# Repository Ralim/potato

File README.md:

# Potato

OpenSource inline USB-PD Power meter.

...WIP...

## Desired features

- Easy to assemble (No QFN)
- Read device PD capabilities
- Capture USB-PD messages
- Read USB D- / D+ voltages for QC
- Pull resistors for QC control
- UART or USB for datalogging
- Either buttons or encoder for input
- Small LCD display
- DC In/Out port

- Accelerometer or tilt switch for rotation?

## Ideas to explore

- As LVGL is a goal for the UI, consider [prototyping](https://docs.lvgl.io/latest/en/html/get-started/pc-simulator.html) on "real" computer or talking to the PineTime team about their experience about developing [UI in NaCL](https://github.com/AppKaki/lvgl-wasm), allowing feedback from web users. If realized, this may allow more explorative development in a less painful environment as you can skip the slow upload/reboot cycle.

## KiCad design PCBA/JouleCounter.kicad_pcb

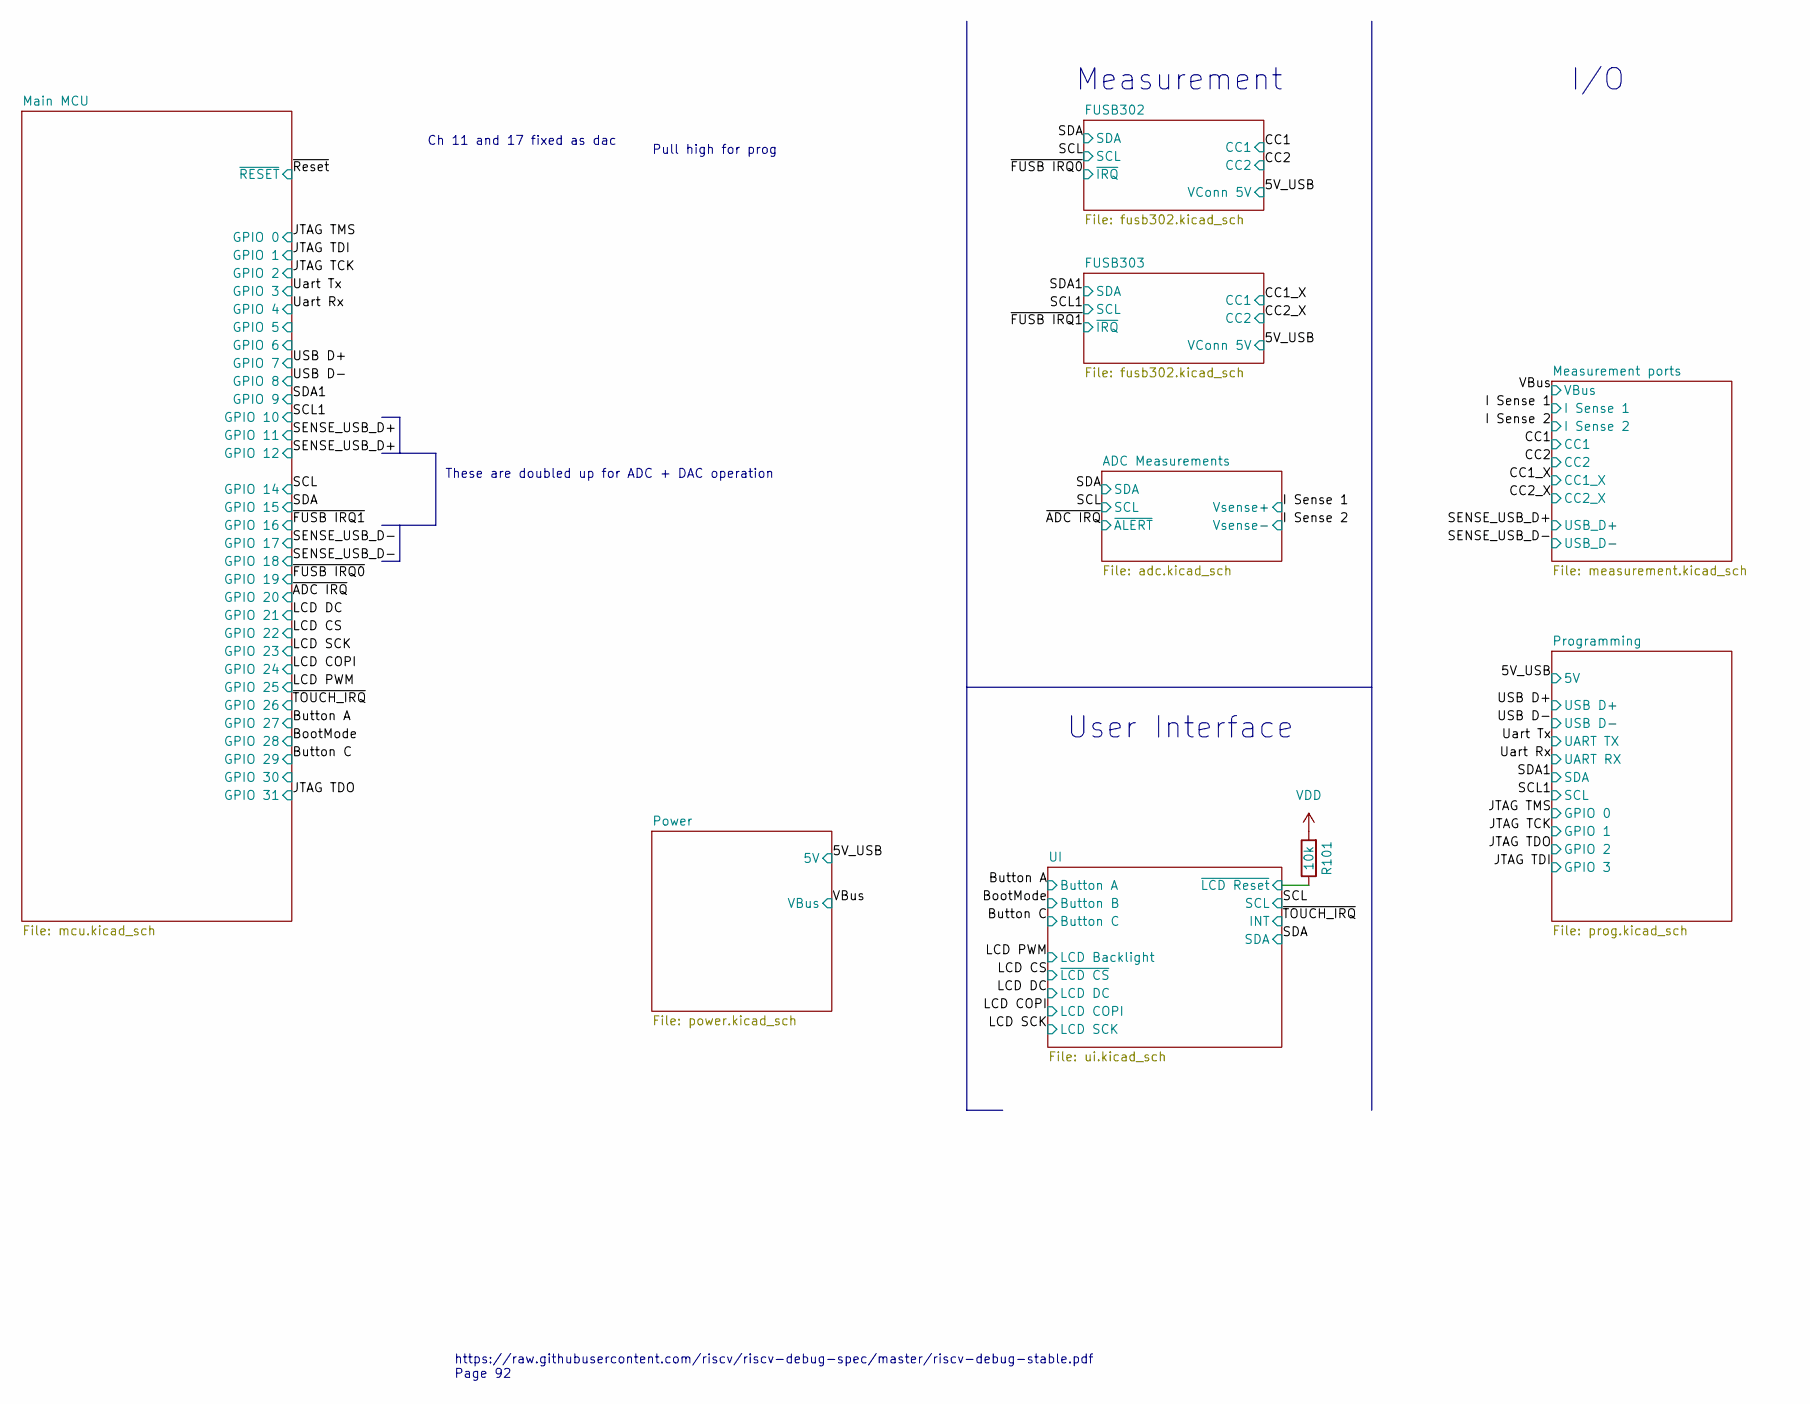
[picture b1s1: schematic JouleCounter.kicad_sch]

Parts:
R101: 10k; R_0603_1608Metric

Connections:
/UI/~LCD Reset: R101.1; also elsewhere on the board
VDD: R101.2; also elsewhere on the board

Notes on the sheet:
Measurement
Pull high for prog
I/O
Ch 11 and 17 fixed as dac
https://raw.githubusercontent.com/riscv/riscv-debug-spec/master/riscv-debug-stable.pdf Page 92
These are doubled up for ADC + DAC operation
User Interface

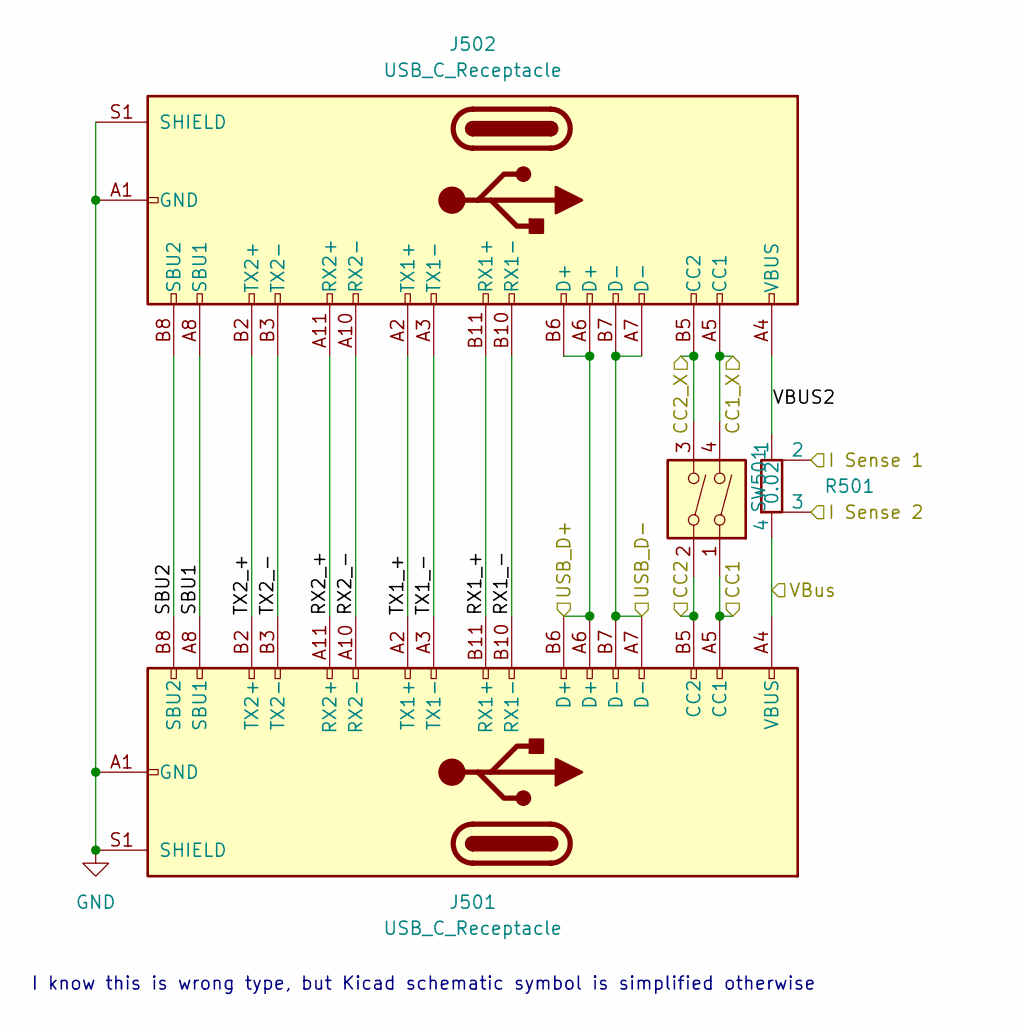
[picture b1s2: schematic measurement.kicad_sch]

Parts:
J501: USB_C_Receptacle; USB_C_Plug_JAE_DX07P024AJ1
J502: USB_C_Receptacle; USB_C_Receptacle_Amphenol_12401610E4-2A
R501: 0.02; R_Shunt_Vishay_WSK2512_6332Metric_T1.19mm
SW501: SW_DIP_x02; SW_DIP_SPSTx02_Slide_Copal_CHS-02A_W5.08mm_P1.27mm_JPin

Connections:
/CC1: J501.A5 (CC1), SW501.1; also elsewhere on the board
/CC1_X: J502.A5 (CC1), SW501.4; also elsewhere on the board
/CC2: J501.B5 (CC2), SW501.2; also elsewhere on the board
/CC2_X: J502.B5 (CC2), SW501.3; also elsewhere on the board
/I Sense 1: R501.2; also elsewhere on the board
/I Sense 2: R501.3; also elsewhere on the board
/Measurement ports/RX1_+: J501.B11 (RX1+), J502.B11 (RX1+)
/Measurement ports/RX1_-: J501.B10 (RX1-), J502.B10 (RX1-)
/Measurement ports/RX2_+: J501.A11 (RX2+), J502.A11 (RX2+)
/Measurement ports/RX2_-: J501.A10 (RX2-), J502.A10 (RX2-)
/Measurement ports/SBU1: J501.A8 (SBU1), J502.A8 (SBU1)
/Measurement ports/SBU2: J501.B8 (SBU2), J502.B8 (SBU2)
/Measurement ports/TX1_+: J501.A2 (TX1+), J502.A2 (TX1+)
/Measurement ports/TX1_-: J501.A3 (TX1-), J502.A3 (TX1-)
/Measurement ports/TX2_+: J501.B2 (TX2+), J502.B2 (TX2+)
/Measurement ports/TX2_-: J501.B3 (TX2-), J502.B3 (TX2-)
/Measurement ports/VBUS2: J502.A4 (VBUS), J502.A9 (VBUS), J502.B4 (VBUS), J502.B9 (VBUS), R501.1
/SENSE_USB_D+: J501.A6 (D+), J501.B6 (D+), J502.A6 (D+), J502.B6 (D+); also elsewhere on the board
/SENSE_USB_D-: J501.A7 (D-), J501.B7 (D-), J502.A7 (D-), J502.B7 (D-); also elsewhere on the board
/VBus: J501.A4 (VBUS), J501.A9 (VBUS), J501.B4 (VBUS), J501.B9 (VBUS), R501.4; also elsewhere on the board
GND: J501.A1 (GND), J501.A12 (GND), J501.B1 (GND), J501.B12 (GND), J501.S1 (SHIELD), J502.A1 (GND), J502.A12 (GND), J502.B1 (GND), J502.B12 (GND), J502.S1 (SHIELD); also elsewhere on the board

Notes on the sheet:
I know this is wrong type, but Kicad schematic symbol is simplified otherwise

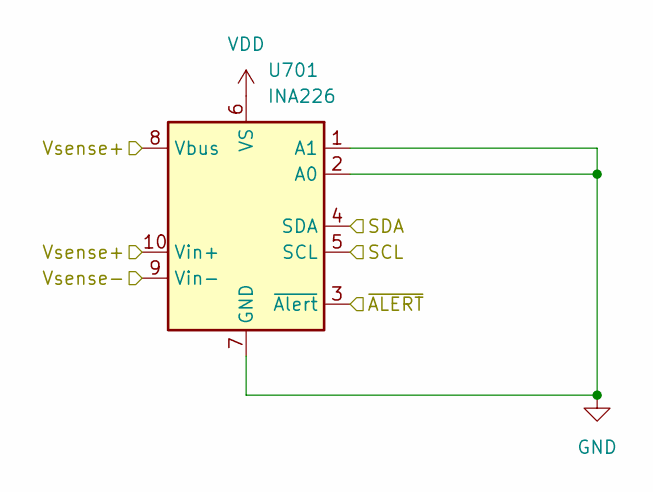
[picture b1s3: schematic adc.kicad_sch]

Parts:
U701: INA226; VSSOP-10_3x3mm_P0.5mm

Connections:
/I Sense 1: U701.8 (Vbus), U701.10 (Vin+); also elsewhere on the board
/I Sense 2: U701.9 (Vin-); also elsewhere on the board
/SCL: U701.5 (SCL); also elsewhere on the board
/SDA: U701.4 (SDA); also elsewhere on the board
/~ADC IRQ: U701.3 (~Alert); also elsewhere on the board
GND: U701.1 (A1), U701.2 (A0), U701.7 (GND); also elsewhere on the board
VDD: U701.6 (VS); also elsewhere on the board

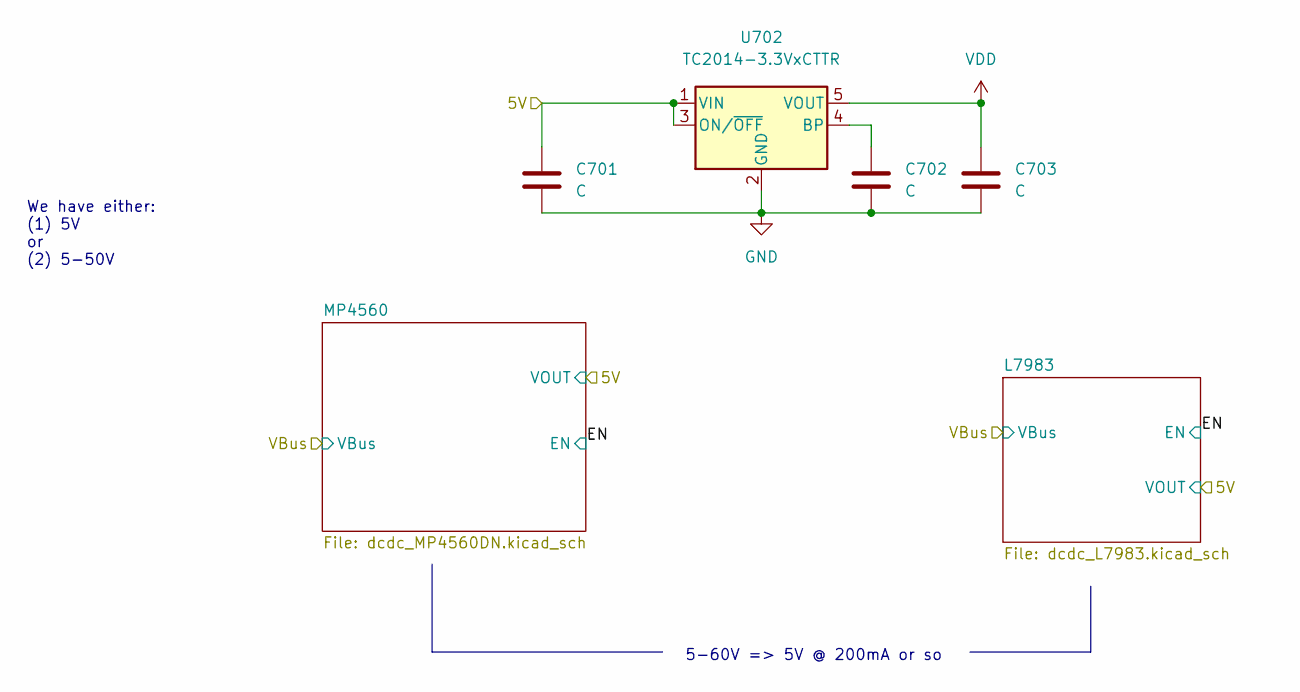
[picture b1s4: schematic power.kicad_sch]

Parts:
C701, C702, C703: C; C_0603_1608Metric
U702: TC2014-3.3VxCTTR; SOT-23-5

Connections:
/5V_USB: C701.1, U702.1 (VIN), U702.3 (ON/~OFF); also elsewhere on the board
GND: C701.2, C702.2, C703.2, U702.2 (GND); also elsewhere on the board
unnamed: C702.1, U702.4 (BP)
VDD: C703.1, U702.5 (VOUT); also elsewhere on the board

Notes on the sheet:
We have either: (1) 5V or (2) 5-50V
5-60V => 5V @ 200mA or so

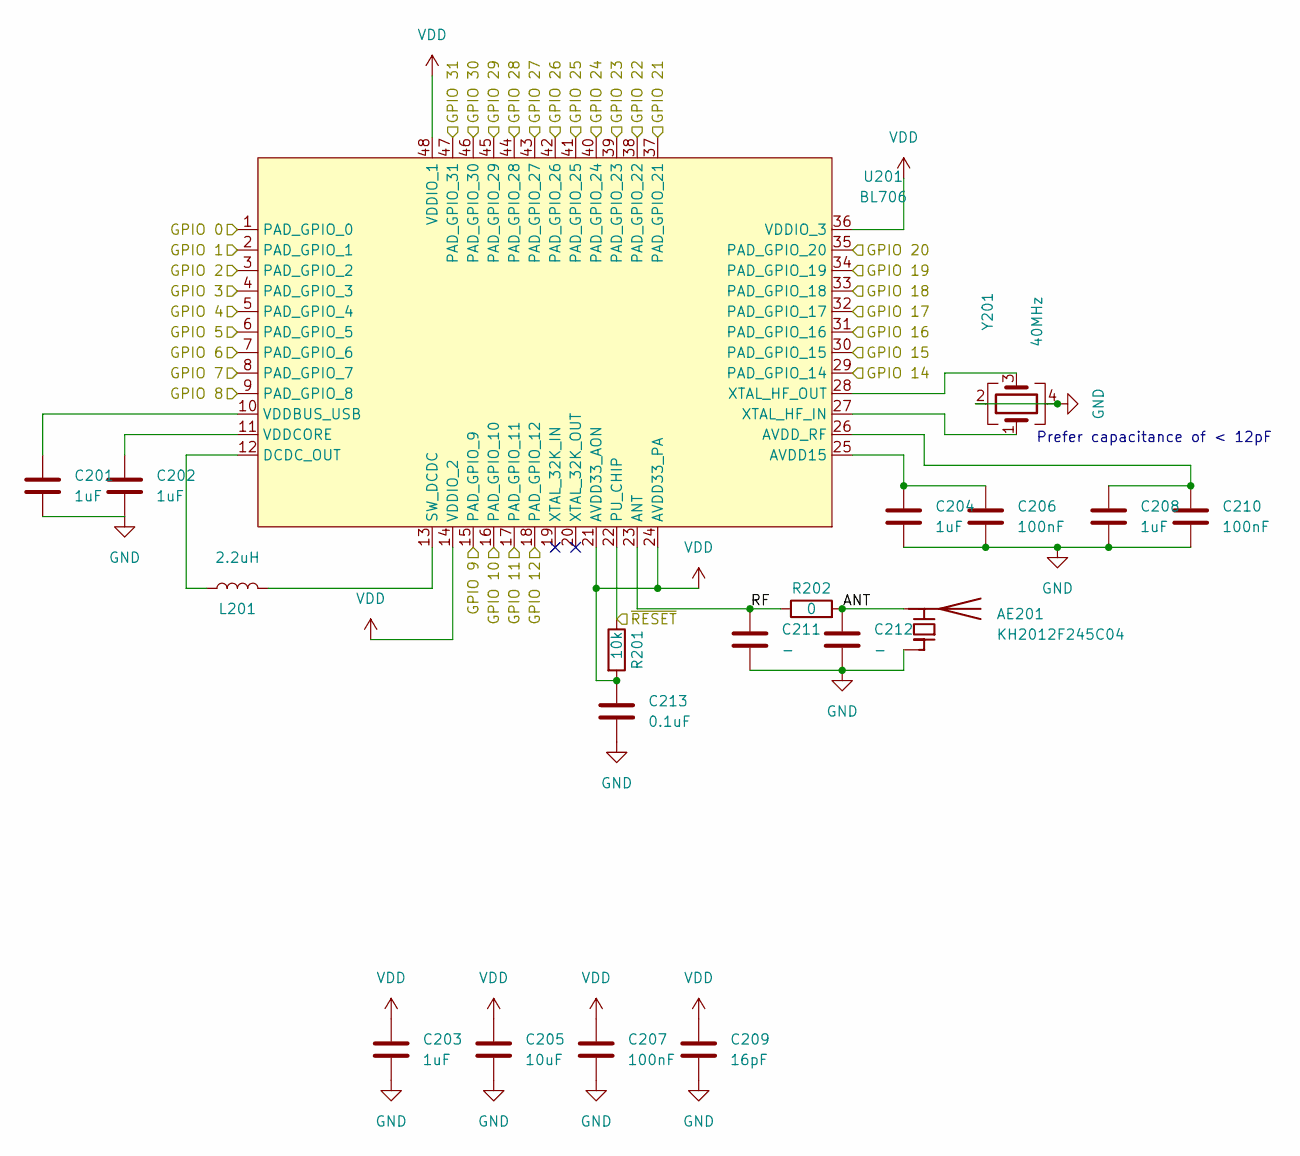
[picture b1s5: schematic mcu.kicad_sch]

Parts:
AE201: KH2012F245C04; R_0805_2012Metric
C201, C202, C203, C204, C208: 1uF; C_0603_1608Metric
C205: 10uF; C_0603_1608Metric
C206, C207, C210: 100nF; C_0603_1608Metric
C209: 16pF; C_0603_1608Metric
C211, C212: -; C_0603_1608Metric
C213: 0.1uF; C_0603_1608Metric
L201: 2.2uH; L_0805_2012Metric
R201: 10k; R_0603_1608Metric
R202: 0; R_0603_1608Metric
U201: BL706; QFN-48-1EP_6x6mm_P0.4mm_EP4.2x4.2mm
Y201: 40MHz; Crystal_SMD_2016-4Pin_2.0x1.6mm

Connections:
/BootMode: U201.44 (PAD_GPIO_28); also elsewhere on the board
/Button A: U201.43 (PAD_GPIO_27); also elsewhere on the board
/Button C: U201.45 (PAD_GPIO_29); also elsewhere on the board
/JTAG TCK: U201.3 (PAD_GPIO_2); also elsewhere on the board
/JTAG TDI: U201.2 (PAD_GPIO_1); also elsewhere on the board
/JTAG TDO: U201.47 (PAD_GPIO_31); also elsewhere on the board
/JTAG TMS: U201.1 (PAD_GPIO_0); also elsewhere on the board
/LCD COPI: U201.40 (PAD_GPIO_24); also elsewhere on the board
/LCD CS: U201.38 (PAD_GPIO_22); also elsewhere on the board
/LCD DC: U201.37 (PAD_GPIO_21); also elsewhere on the board
/LCD PWM: U201.41 (PAD_GPIO_25); also elsewhere on the board
/LCD SCK: U201.39 (PAD_GPIO_23); also elsewhere on the board
/Main MCU/ANT: AE201.2 (PCB_Trace), C212.1, R202.2
/Main MCU/GPIO 5: U201.6 (PAD_GPIO_5)
/Main MCU/GPIO 6: U201.7 (PAD_GPIO_6)
/Main MCU/GPIO 30: U201.46 (PAD_GPIO_30)
/Main MCU/RF: C211.1, R202.1, U201.23 (ANT)
/SCL: U201.29 (PAD_GPIO_14); also elsewhere on the board
/SCL1: U201.16 (PAD_GPIO_10); also elsewhere on the board
/SDA: U201.30 (PAD_GPIO_15); also elsewhere on the board
/SDA1: U201.15 (PAD_GPIO_9); also elsewhere on the board
/SENSE_USB_D+: U201.17 (PAD_GPIO_11), U201.18 (PAD_GPIO_12); also elsewhere on the board
/SENSE_USB_D-: U201.32 (PAD_GPIO_17), U201.33 (PAD_GPIO_18); also elsewhere on the board
/USB D+: U201.8 (PAD_GPIO_7); also elsewhere on the board
/USB D-: U201.9 (PAD_GPIO_8); also elsewhere on the board
/Uart Rx: U201.5 (PAD_GPIO_4); also elsewhere on the board
/Uart Tx: U201.4 (PAD_GPIO_3); also elsewhere on the board
/~ADC IRQ: U201.35 (PAD_GPIO_20); also elsewhere on the board
/~FUSB IRQ0: U201.34 (PAD_GPIO_19); also elsewhere on the board
/~FUSB IRQ1: U201.31 (PAD_GPIO_16); also elsewhere on the board
/~Reset: R201.1, U201.22 (PU_CHIP)
/~TOUCH_IRQ: U201.42 (PAD_GPIO_26); also elsewhere on the board
GND: AE201.1 (FEED), C201.2, C202.2, C203.2, C204.2, C205.2, C206.2, C207.2, C208.2, C209.2, C210.2, C211.2, C212.2, C213.2, Y201.2, Y201.4; also elsewhere on the board
unnamed: C201.1, U201.10 (VDDBUS_USB)
unnamed: C202.1, U201.11 (VDDCORE)
unnamed: C204.1, C206.1, U201.25 (AVDD15)
unnamed: C208.1, C210.1, U201.26 (AVDD_RF)
unnamed: L201.1, U201.12 (DCDC_OUT)
unnamed: L201.2, U201.13 (SW_DCDC)
unnamed: U201.27 (XTAL_HF_IN), Y201.1
unnamed: U201.28 (XTAL_HF_OUT), Y201.3
VDD: C203.1, C205.1, C207.1, C209.1, C213.1, R201.2, U201.14 (VDDIO_2), U201.21 (AVDD33_AON), U201.24 (AVDD33_PA), U201.36 (VDDIO_3), U201.48 (VDDIO_1); also elsewhere on the board

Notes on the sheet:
Prefer capacitance of < 12pF

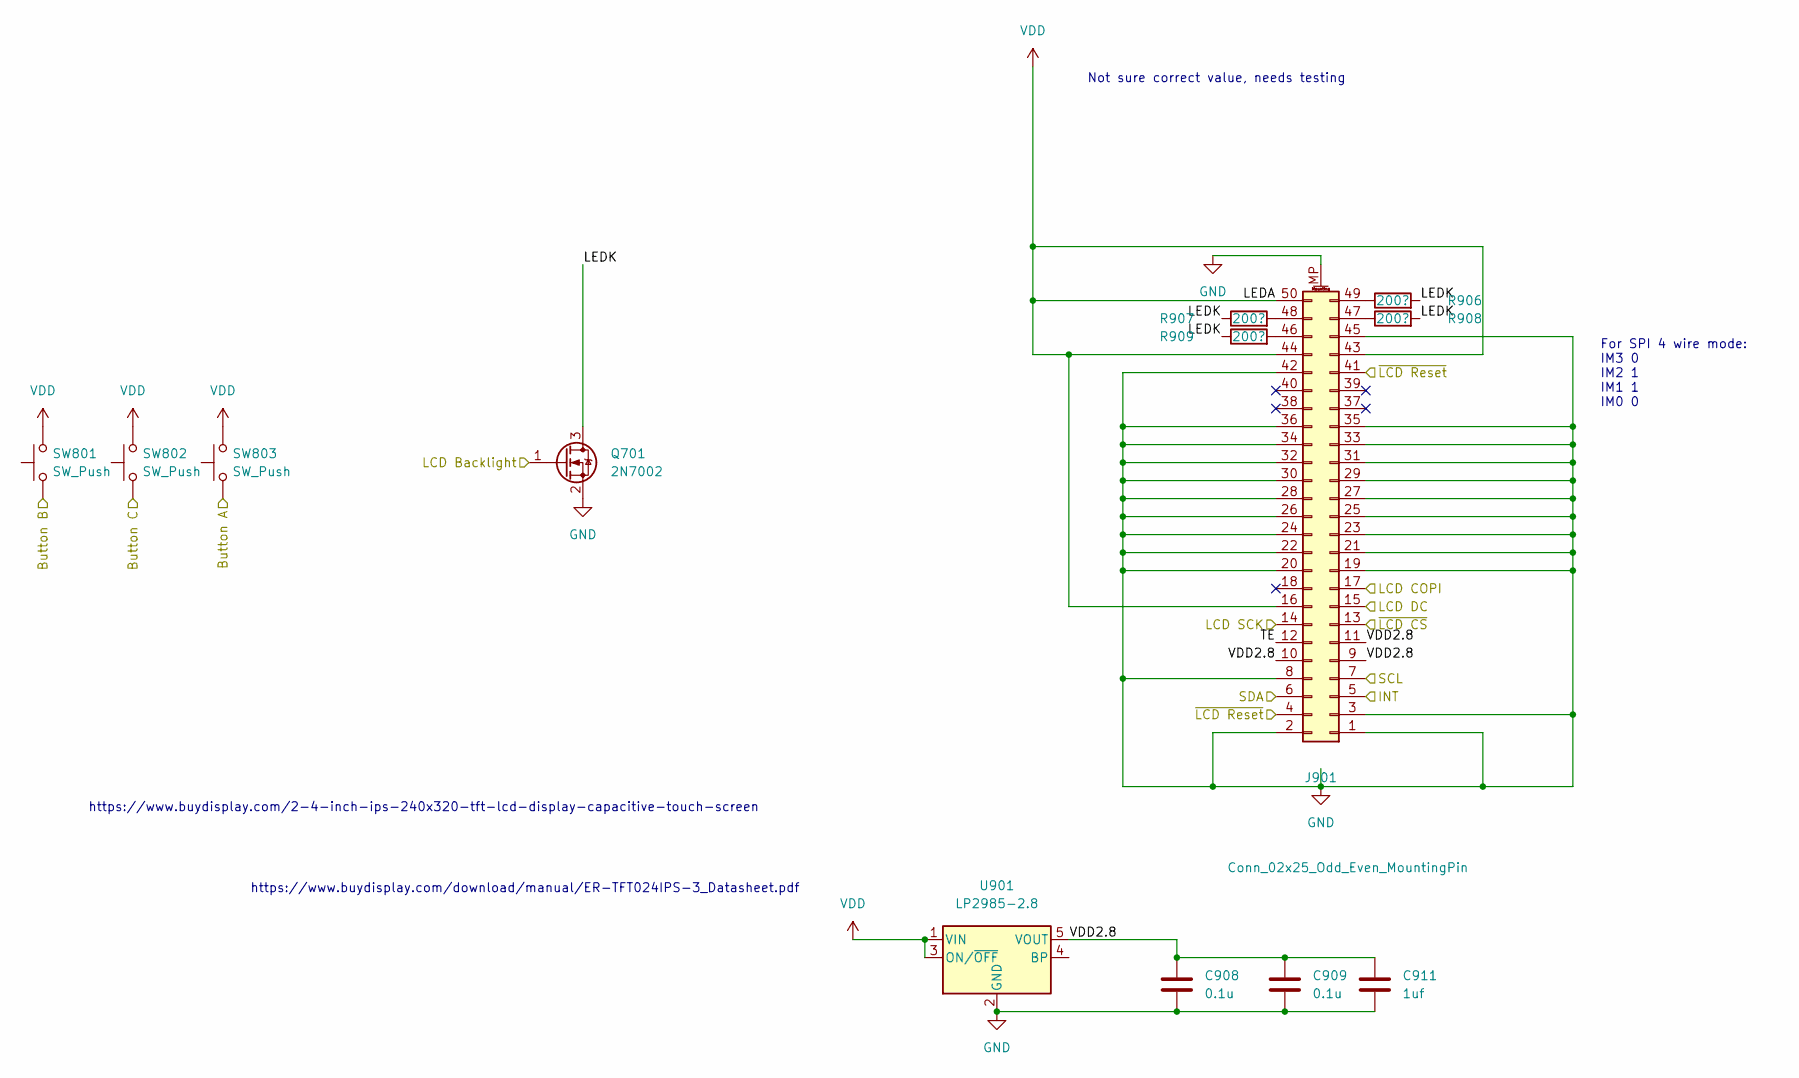
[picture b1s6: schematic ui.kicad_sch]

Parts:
C908, C909: 0.1u; C_0603_1608Metric
C911: 1uf; C_0603_1608Metric
J901: Conn_02x25_Odd_Even_MountingPin; Molex_54132-5033_1x50-1MP_P0.5mm_Horizontal
Q701: 2N7002; SOT-23
R906, R907, R908, R909: 200?; R_0603_1608Metric
SW801, SW802, SW803: SW_Push; SW_Tactile_SKHH_Angled
U901: LP2985-2.8; SOT-23-5

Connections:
/BootMode: SW801.1; also elsewhere on the board
/Button A: SW803.1; also elsewhere on the board
/Button C: SW802.1; also elsewhere on the board
/LCD COPI: J901.17; also elsewhere on the board
/LCD CS: J901.13; also elsewhere on the board
/LCD DC: J901.15; also elsewhere on the board
/LCD PWM: Q701.1 (G); also elsewhere on the board
/LCD SCK: J901.14; also elsewhere on the board
/SCL: J901.7; also elsewhere on the board
/SDA: J901.6; also elsewhere on the board
/UI/LEDK: Q701.3 (D), R906.2, R907.1, R908.2, R909.1
/UI/TE: J901.12
/UI/VDD2.8: C908.1, C909.1, C911.1, J901.9, J901.10, J901.11, U901.5 (VOUT)
/UI/~LCD Reset: J901.4, J901.41; also elsewhere on the board
/~TOUCH_IRQ: J901.5; also elsewhere on the board
GND: C908.2, C909.2, C911.2, J901.1, J901.2, J901.3, J901.8, J901.19, J901.20, J901.21, J901.22, J901.23, J901.24, J901.25, J901.26, J901.27, J901.28, J901.29, J901.30, J901.31, J901.32, J901.33, J901.34, J901.35, J901.36, J901.42, J901.45, J901.MP (MountPin), Q701.2 (S), U901.2 (GND); also elsewhere on the board
unnamed: J901.46, R909.2
unnamed: J901.47, R908.1
unnamed: J901.48, R907.2
unnamed: J901.49, R906.1
VDD: J901.16, J901.43, J901.44, J901.50, SW801.2, SW802.2, SW803.2, U901.1 (VIN), U901.3 (ON/~OFF); also elsewhere on the board

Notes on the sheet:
Not sure correct value, needs testing
https://www.buydisplay.com/2-4-inch-ips-240x320-tft-lcd-display-capacitive-touch-screen
For SPI 4 wire mode: IM3 0 IM2 1 IM1 1 IM0 0
https://www.buydisplay.com/download/manual/ER-TFT024IPS-3_Datasheet.pdf

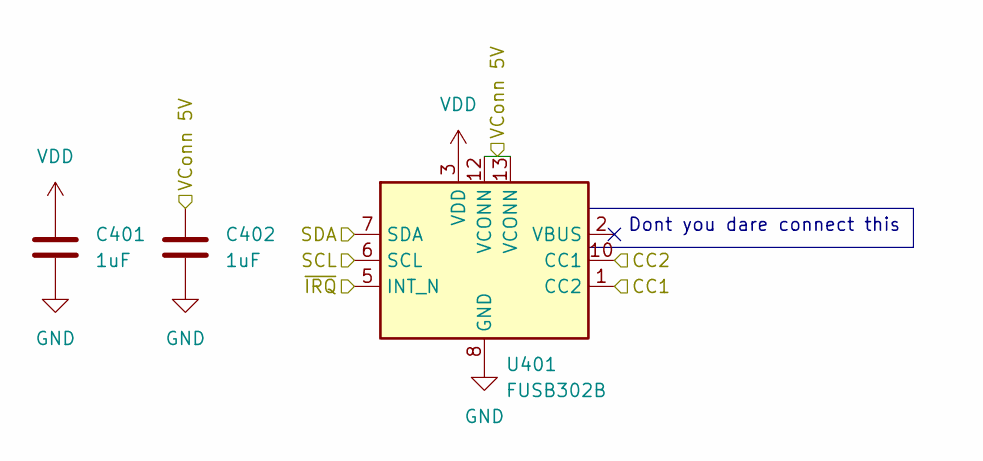
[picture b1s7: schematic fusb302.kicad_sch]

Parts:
C401, C402: 1uF; C_0603_1608Metric
U401: FUSB302B; WQFN-14-1EP_2.5x2.5mm_P0.5mm_EP1.45x1.45mm

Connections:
/5V_USB: C402.1, U401.12 (VCONN), U401.13 (VCONN); also elsewhere on the board
/CC1: U401.1 (CC2), U401.14 (CC2); also elsewhere on the board
/CC2: U401.10 (CC1), U401.11 (CC1); also elsewhere on the board
/SCL: U401.6 (SCL); also elsewhere on the board
/SDA: U401.7 (SDA); also elsewhere on the board
/~FUSB IRQ0: U401.5 (INT_N); also elsewhere on the board
GND: C401.2, C402.2, U401.8 (GND), U401.9 (GND), U401.15 (GND); also elsewhere on the board
VDD: C401.1, U401.3 (VDD), U401.4 (VDD); also elsewhere on the board

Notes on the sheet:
Dont you dare connect this

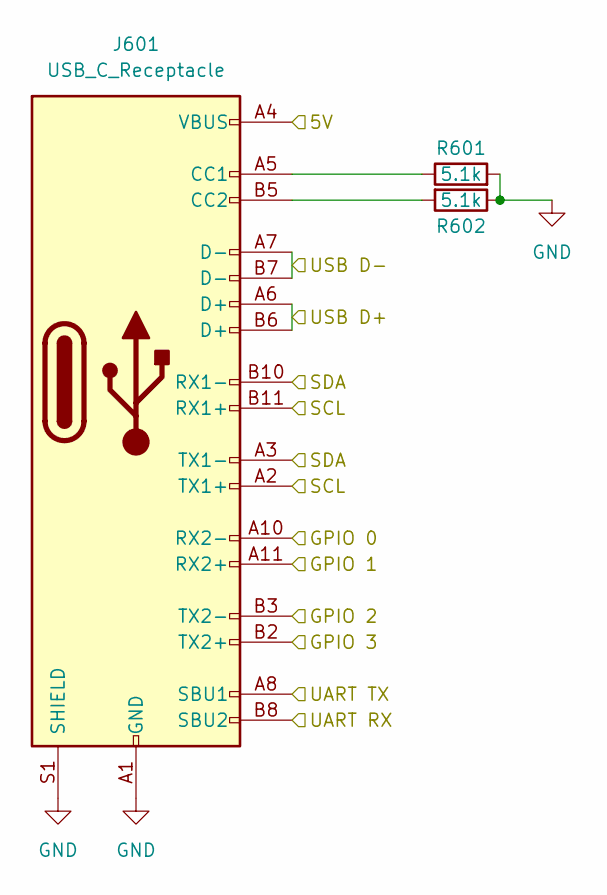
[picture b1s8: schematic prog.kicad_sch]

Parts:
J601: USB_C_Receptacle; USB_C_Receptacle_Amphenol_12401610E4-2A
R601, R602: 5.1k; R_0603_1608Metric

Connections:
/5V_USB: J601.A4 (VBUS), J601.A9 (VBUS), J601.B4 (VBUS), J601.B9 (VBUS); also elsewhere on the board
/JTAG TCK: J601.A11 (RX2+); also elsewhere on the board
/JTAG TDI: J601.B2 (TX2+); also elsewhere on the board
/JTAG TDO: J601.B3 (TX2-); also elsewhere on the board
/JTAG TMS: J601.A10 (RX2-); also elsewhere on the board
/SCL1: J601.A2 (TX1+), J601.B11 (RX1+); also elsewhere on the board
/SDA1: J601.A3 (TX1-), J601.B10 (RX1-); also elsewhere on the board
/USB D+: J601.A6 (D+), J601.B6 (D+); also elsewhere on the board
/USB D-: J601.A7 (D-), J601.B7 (D-); also elsewhere on the board
/Uart Rx: J601.B8 (SBU2); also elsewhere on the board
/Uart Tx: J601.A8 (SBU1); also elsewhere on the board
GND: J601.A1 (GND), J601.A12 (GND), J601.B1 (GND), J601.B12 (GND), J601.S1 (SHIELD), R601.2, R602.1; also elsewhere on the board
unnamed: J601.A5 (CC1), R601.1
unnamed: J601.B5 (CC2), R602.2

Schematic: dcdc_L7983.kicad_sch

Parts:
C1001: 100nF; C_0603_1608Metric
C1002, C1003, C1004: 2.2uF; C_0603_1608Metric
C1005: C; C_0603_1608Metric
IC1001: L7983PU33R; Manufacturer_Part_Number L7983PU33R; Mouser Part Number 511-L7983PU33R
L1001: 47uH; L_1210_3225Metric
R1001, R1003: 0; R_0603_1608Metric
R1002: DNP; R_0603_1608Metric
R1004: 100k; R_0603_1608Metric
R1005: 180k; R_0603_1608Metric
R1006: 68k; R_0603_1608Metric

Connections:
/5V_USB: C1003.1, C1004.1, L1001.2, R1005.1; also elsewhere on the board
/Power/EN: IC1001.7 (EN/UVLO); also elsewhere on the board
/Power/L7983/Lx: IC1001.9 (LX), L1001.1
/VBus: C1005.1, IC1001.8 (VIN); also elsewhere on the board
GND: C1001.2, C1002.2, C1003.2, C1005.2, IC1001.5 (LNM/~LCM), IC1001.10 (GND), IC1001.11 (E.P.), R1002.2, R1006.2; also elsewhere on the board
unnamed: C1001.1, IC1001.2 (VBIAS), R1001.2, R1002.1
unnamed: C1002.1, IC1001.3 (VCC), R1003.1, R1004.1
unnamed: C1004.2, IC1001.1 (VOUT/FB), R1001.1, R1005.2, R1006.1
unnamed: IC1001.4 (FSW), R1003.2
unnamed: IC1001.6 (~RST), R1004.2

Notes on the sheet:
https://www.lcsc.com/product-detail/Inductors-SMD_TDK-NLCV32T-470K-PF_C83083.html

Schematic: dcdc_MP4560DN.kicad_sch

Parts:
C901: 47uF; C_0603_1608Metric
C902, C906: 4.7uF; C_0603_1608Metric
C903, C904: -; C_0603_1608Metric
C905: 100nF; C_0603_1608Metric
D901: D_Schottky; D_SOD-323
IC901: MP4560DN-LF-Z; SOIC127P600X170-9N; Manufacturer_Part_Number MP4560DN-LF-Z; Mouser Part Number 946-MP4560DNLFZ
L901: 15; L_Wuerth_MAPI-3010
R901, R904, R905: 200k; R_0603_1608Metric
R902, R903: -; R_0603_1608Metric

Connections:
/5V_USB: C901.2, C902.2, L901.1, R901.1; also elsewhere on the board
/Power/EN: IC901.2 (EN), R904.1; also elsewhere on the board
/VBus: C906.2, IC901.7 (VIN), R904.2; also elsewhere on the board
GND: C901.1, C902.1, C904.1, C906.1, D901.2 (A), IC901.5 (GND), IC901.9 (EP), R902.2, R903.2, R905.2; also elsewhere on the board
unnamed: C903.1, R903.1
unnamed: C903.2, C904.2, IC901.3 (COMP)
unnamed: C905.1, D901.1 (K), IC901.1 (SW), L901.2
unnamed: C905.2, IC901.8 (BST)
unnamed: IC901.4 (FB), R901.2, R902.1
unnamed: IC901.6 (FREQ), R905.1

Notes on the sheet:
https://lcsc.com/product-detail/Power-Inductors_CENKER-CKCS3012-15uH-M_C354559.html

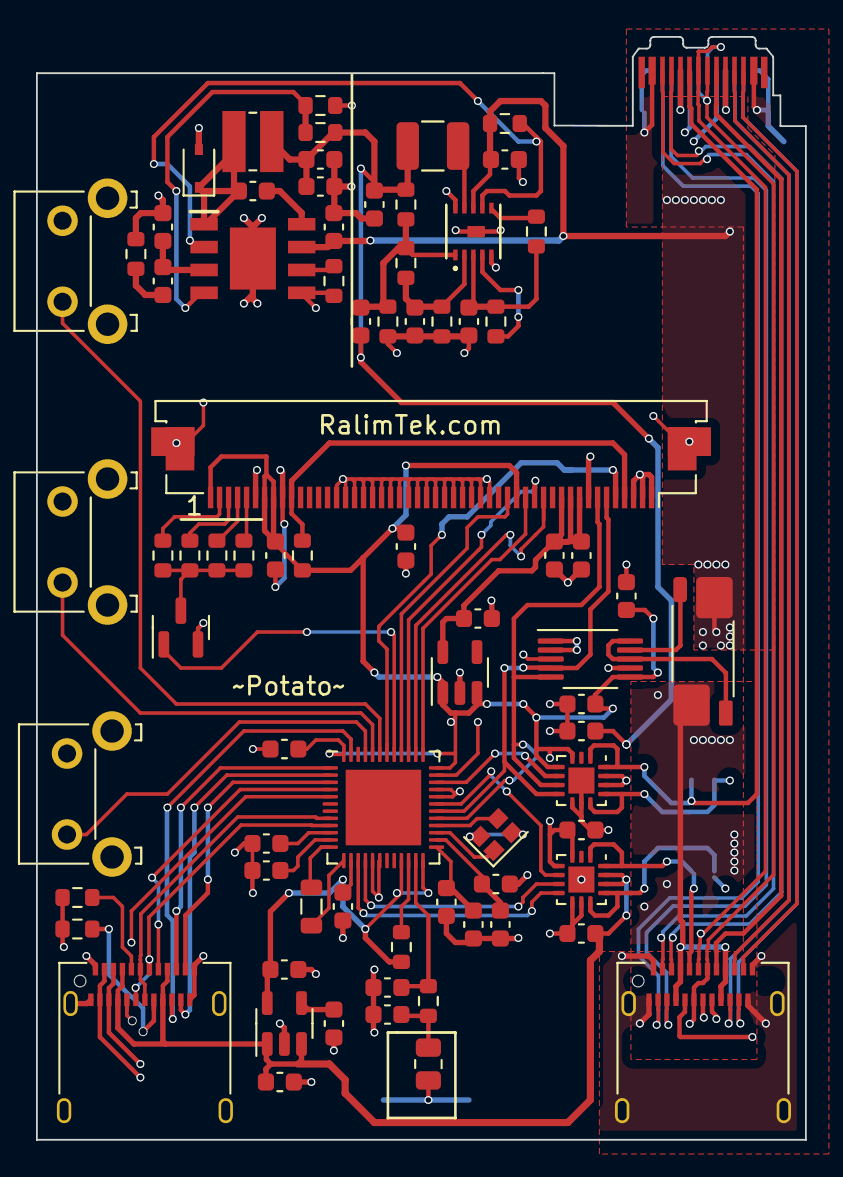
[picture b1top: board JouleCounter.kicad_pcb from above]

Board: 4 copper layers, 42.7 x 61.3 mm, 78 parts (1 on the bottom side), 81 nets.

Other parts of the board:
C301, C302: 1uF; C_0603_1608Metric
U301: FUSB302B; WQFN-14-1EP_2.5x2.5mm_P0.5mm_EP1.45x1.45mm

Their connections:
/5V_USB: C302.1, U301.12 (VCONN), U301.13 (VCONN); also elsewhere on the board
/CC1_X: U301.1 (CC2), U301.14 (CC2); also elsewhere on the board
/CC2_X: U301.10 (CC1), U301.11 (CC1); also elsewhere on the board
/SCL1: U301.6 (SCL); also elsewhere on the board
/SDA1: U301.7 (SDA); also elsewhere on the board
/~FUSB IRQ1: U301.5 (INT_N); also elsewhere on the board
GND: C301.2, C302.2, U301.8 (GND), U301.9 (GND), U301.15 (GND); also elsewhere on the board
VDD: C301.1, U301.3 (VDD), U301.4 (VDD); also elsewhere on the board

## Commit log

2022-03-03 Create BL604 symbol
2022-03-03 Scratching out schematic
2022-03-03 Input/output jacks
2022-03-03 Programming uart added
2022-03-03 ADC readings
2022-03-03 TODO: usb c plug
2022-03-04 Right usb end
2022-03-04 More schematics
2022-03-05 Add link to screen
2022-03-05 Add Qwiic
2022-03-05 Start adding power
2022-03-13 Adding DC/DC layout
2022-03-13 GPIO association pass 1
2022-03-14 Create Documents
2022-03-14 Add an empty directory for RB.
2022-03-14 Propose accelerometer
2022-03-14 Add 'ideas to explore'
2022-03-26 Add MP4560 schematic symbol+footprint
2022-03-27 Finish MP schematic
2022-03-27 Assign footprints
2022-08-10 Update schematic pinmap bl706
2022-08-20 Make bl706 symbol
2022-08-20 Rough outline
2022-08-20 More rough placement
2022-08-20 Routing
2022-08-20 Step models for ports
2022-09-03 PCB size
2022-09-03 molex model
2022-09-03 Jtag on usb-c
2022-09-10 Finish routing
2022-09-21 Fix up via hole size
